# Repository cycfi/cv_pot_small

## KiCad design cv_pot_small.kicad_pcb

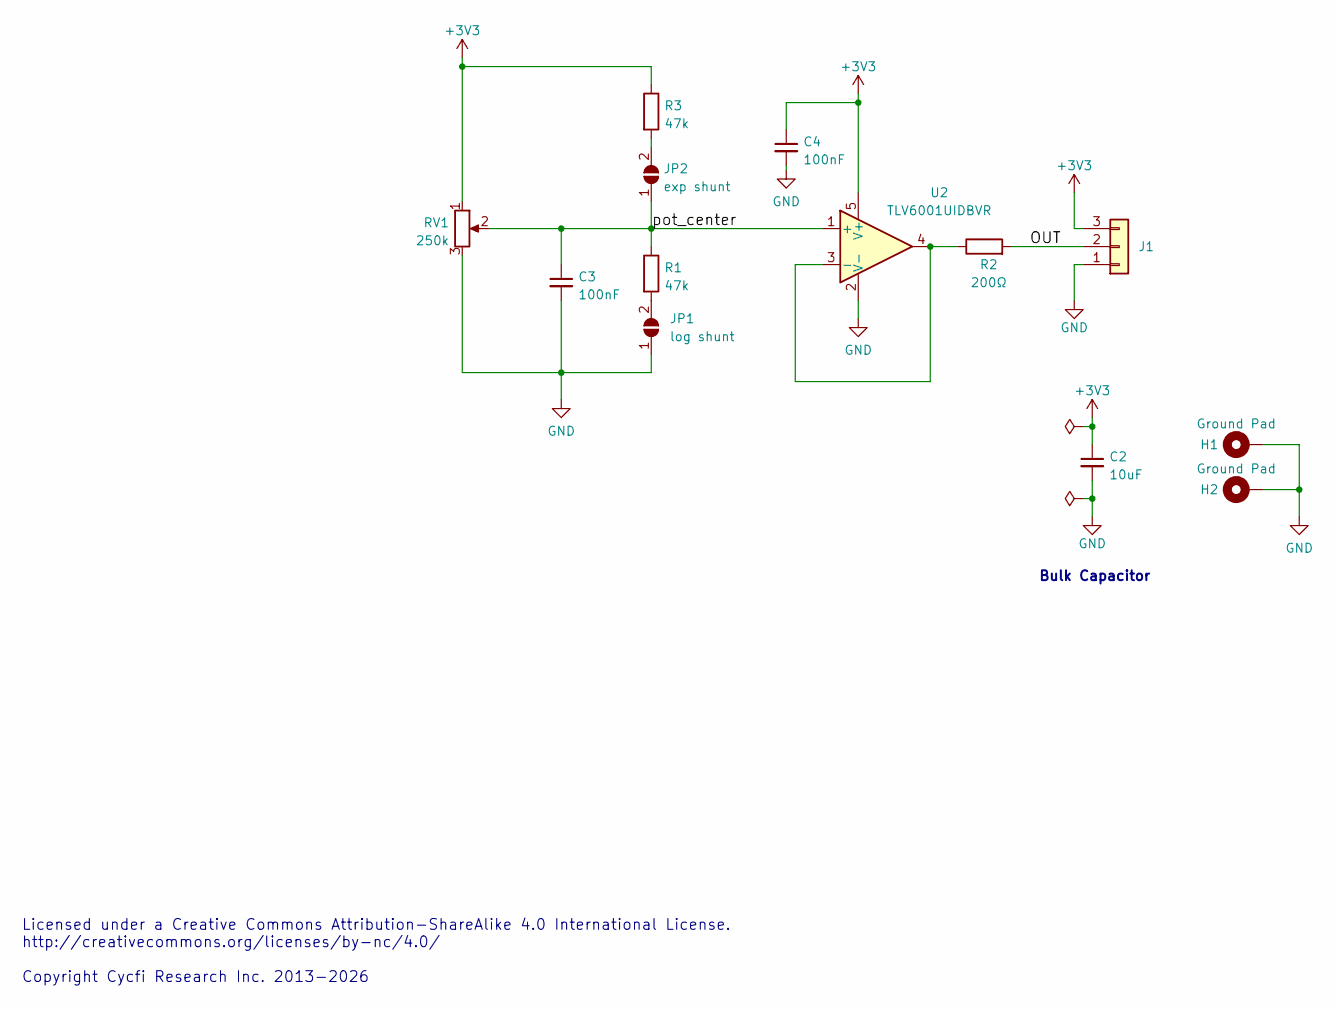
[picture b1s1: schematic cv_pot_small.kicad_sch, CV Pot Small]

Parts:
C2: 10uF; C_0805_2012Metric; LCSC C15850
C3, C4: 100nF; C_0402_1005Metric; LCSC C307331
H1, H2: Ground Pad; single-pad-2x2-circular
J1: I/O connector; JST_SH_SM03B-SRSS-TB_1x03-1MP_P1.00mm_Horizontal; LCSC C160403
JP1: log shunt; SolderJumper-2_P1.3mm_Open_TrianglePad1.0x1.5mm
JP2: exp shunt; SolderJumper-2_P1.3mm_Open_TrianglePad1.0x1.5mm
R1, R3: 47k; R_0402_1005Metric; LCSC C25792
R2: 200Ω; R_0402_1005Metric; LCSC C25087
RV1: 250k; bourns_pdb181
U2: TLV6001UIDBVR; SOT-23-5; LCSC C544299

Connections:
+3V3: C2.1, C4.1, J1.3, R3.1, RV1.1, U2.5 (V+)
/OUT: J1.2, R2.2
/pot_center: C3.1, JP2.1 (A), R1.1, RV1.2, U2.1 (+)
GND: C2.2, C3.2, C4.2, H1.1, H2.1, J1.1, JP1.1 (A), RV1.3, U2.2 (V-)
unnamed: JP1.2 (B), R1.2
unnamed: JP2.2 (B), R3.2
unnamed: R2.1, U2.3 (-), U2.4

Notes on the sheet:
Bulk Capacitor
Licensed under a Creative Commons Attribution-ShareAlike 4.0 International License. http://creativecommons.org/licenses/by-nc/4.0/ Copyright Cycfi Research Inc. 2013-2026

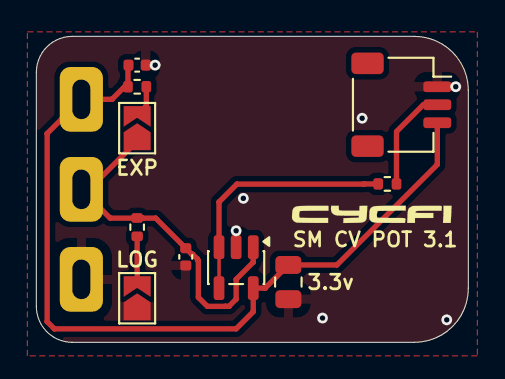
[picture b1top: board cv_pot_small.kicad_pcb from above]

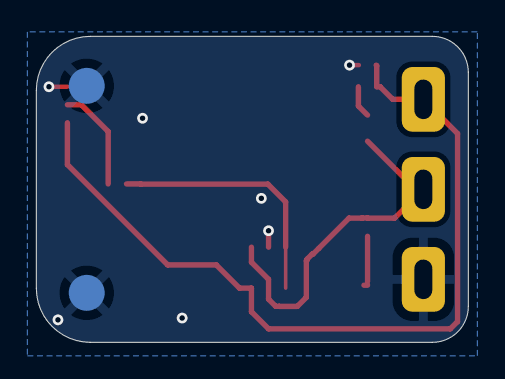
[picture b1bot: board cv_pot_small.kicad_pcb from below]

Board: 2 copper layers, 24.0 x 17.0 mm, 13 parts (2 on the bottom side), 7 nets.

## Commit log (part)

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2022-03-01 Added small CV Pot
2022-04-16 Updated components for JLCPCB PCBA
2022-04-18 PCB fabrication
2022-04-20 Added big CV pot
2022-06-07 Added diode markings in the silkscreen
2022-06-20 Switched to TLV6001UIDBVR Opamp
2023-08-05 Changed taper resistor value
2024-08-06 Added 1k output resistor
